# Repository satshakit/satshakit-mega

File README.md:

<div align="center"><h1 style="font-family: courier;" align="center">satshakit-mega</h1></div>
<div align="center"></div>
<div align="center"><i>An open source & fabbable ATMega2560 based microcontroller board.</i></div>

License
--
This work is licensed under the terms of the open source license: Creative Commons Attribution-ShareAlike 4.0 International ([CC BY-SA 4.0](https://creativecommons.org/licenses/by-sa/4.0/)).

Disclaimer  
--

<div class="align-justify">
This hardware/software is provided "as is", and you use the hardware/software at your own risk. Under no circumstances shall any author be liable for direct, indirect, special, incidental, or consequential damages resulting from the use, misuse, or inability to use this hardware/software, even if the authors have been advised of the possibility of such damages.</div>

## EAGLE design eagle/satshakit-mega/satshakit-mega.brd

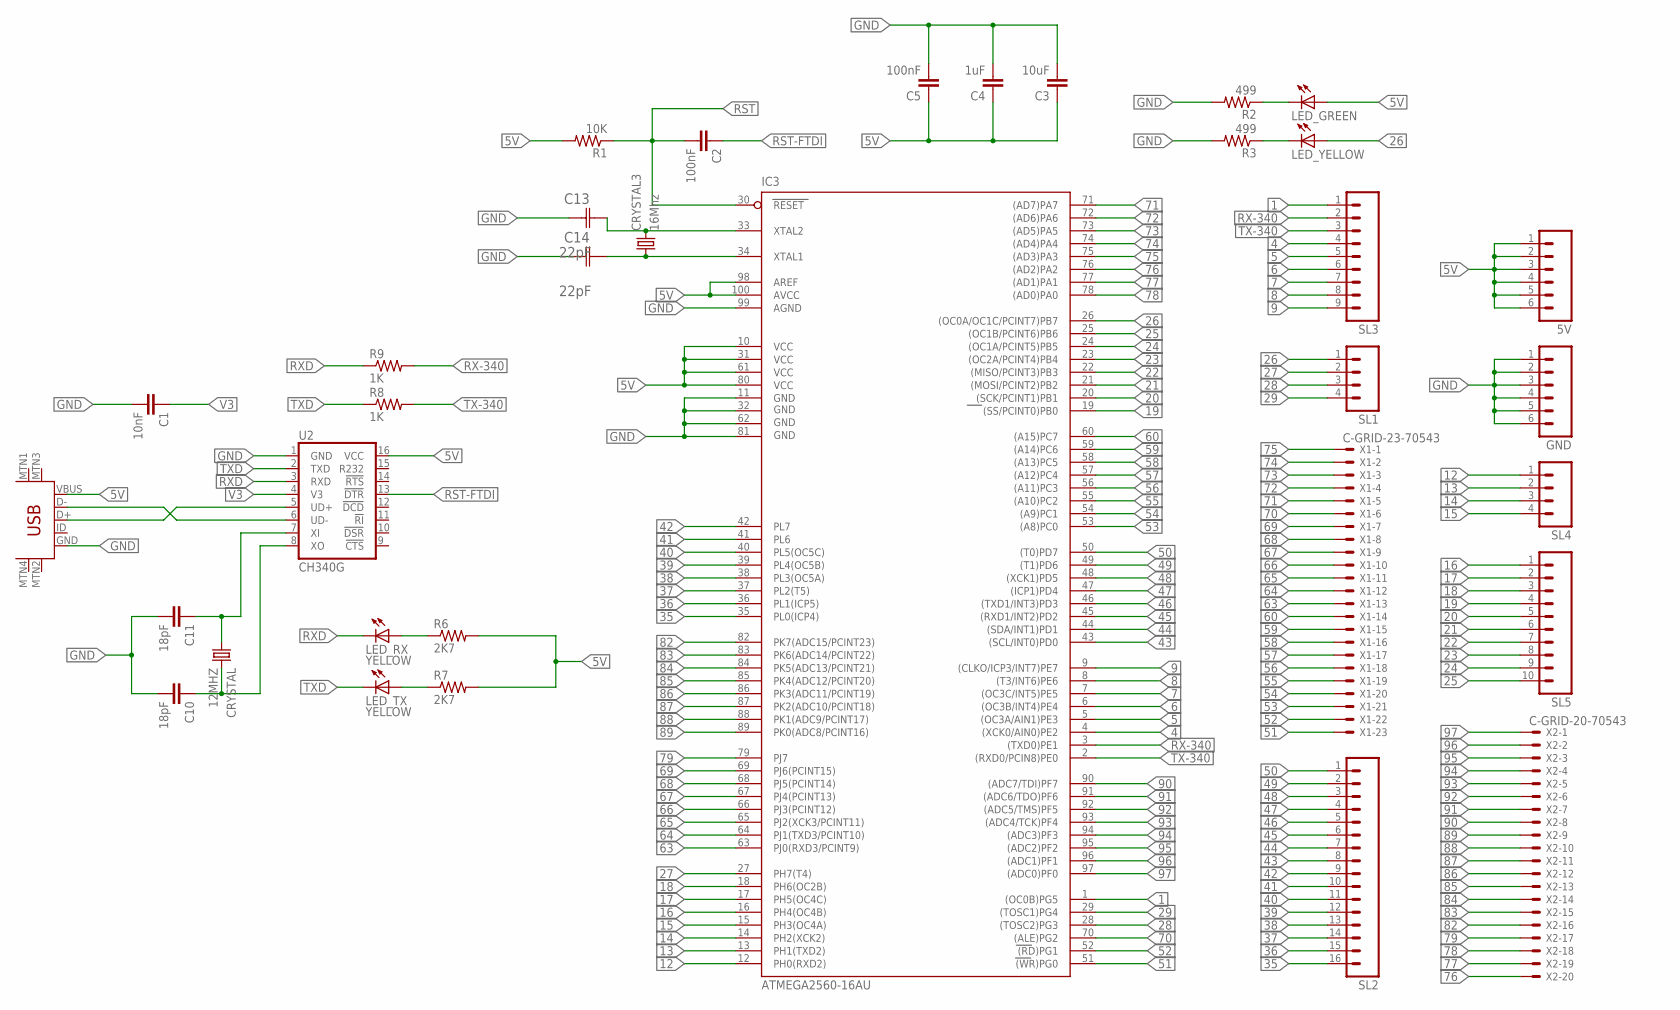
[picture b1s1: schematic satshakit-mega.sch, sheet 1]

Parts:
5V: M06; 06P
C1: 10nF; 1206
C2, C5: 100nF; 1206
C3: 10uF; 1206
C4: 1uF; 1206
C10, C11: 18pF; 1206
C13, C14: 22pF; CAPC3216X178N
CRYSTAL: 12MHZ; CSM-7X-DU
CRYSTAL3: 16Mhz; CSM-7X-DU
GND: M06; 06P
IC3: ATMEGA2560-16AU; TQFP100
LED_GREEN: LED1206; 1206
LED_RX: YELLOW; LED1206
LED_TX: YELLOW; LED1206
LED_YELLOW: LED1206; 1206
R1: 10K; R1206
R2, R3: 499; 1206
R6, R7: 2K7; R1206
R8, R9: 1K; R1206
SL1, SL4: M04; 04P
SL2: M16; 16P
SL3: M09; 09P
SL5: M10; 10P
U2: CH340G; SO016
U$7: USB-MINIB-5PIN; USB-MINIB
X1: C-GRID-23-70543; 70543-23
X2: C-GRID-20-70543; 70543-20

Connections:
1: IC3.1 ((OC0B)PG5), SL3.1
4: IC3.4 ((XCK0/AIN0)PE2), SL3.4
5: IC3.5 ((OC3A/AIN1)PE3), SL3.5
5V: 5V.1, 5V.2, 5V.3, 5V.4, 5V.5, 5V.6, C3.1, C4.1, C5.1, IC3.10 (VCC), IC3.31 (VCC1), IC3.61 (VCC2), IC3.80 (VCC3), IC3.98 (AREF), IC3.100 (AVCC), LED_GREEN.1 (A), R1.2, R6.2, R7.2, U2.16 (VCC), U$7.VBUS
6: IC3.6 ((OC3B/INT4)PE4), SL3.6
7: IC3.7 ((OC3C/INT5)PE5), SL3.7
8: IC3.8 ((T3/INT6)PE6), SL3.8
9: IC3.9 ((CLKO/ICP3/INT7)PE7), SL3.9
12: IC3.12 (PH0(RXD2)), SL4.1
13: IC3.13 (PH1(TXD2)), SL4.2
14: IC3.14 (PH2(XCK2)), SL4.3
15: IC3.15 (PH3(OC4A)), SL4.4
16: IC3.16 (PH4(OC4B)), SL5.1
17: IC3.17 (PH5(OC4C)), SL5.2
18: IC3.18 (PH6(OC2B)), SL5.3
19: IC3.19 ((SS/PCINT0)PB0), SL5.4
20: IC3.20 ((SCK/PCINT1)PB1), SL5.5
21: IC3.21 ((MOSI/PCINT2)PB2), SL5.6
22: IC3.22 ((MISO/PCINT3)PB3), SL5.7
23: IC3.23 ((OC2A/PCINT4)PB4), SL5.8
24: IC3.24 ((OC1A/PCINT5)PB5), SL5.9
25: IC3.25 ((OC1B/PCINT6)PB6), SL5.10
26: IC3.26 ((OC0A/OC1C/PCINT7)PB7), LED_YELLOW.1 (A), SL1.1
27: IC3.27 (PH7(T4)), SL1.2
28: IC3.28 ((TOSC2)PG3), SL1.3
29: IC3.29 ((TOSC1)PG4), SL1.4
35: IC3.35 (PL0(ICP4)), SL2.16
36: IC3.36 (PL1(ICP5)), SL2.15
37: IC3.37 (PL2(T5)), SL2.14
38: IC3.38 (PL3(OC5A)), SL2.13
39: IC3.39 (PL4(OC5B)), SL2.12
40: IC3.40 (PL5(OC5C)), SL2.11
41: IC3.41 (PL6), SL2.10
42: IC3.42 (PL7), SL2.9
43: IC3.43 ((SCL/INT0)PD0), SL2.8
44: IC3.44 ((SDA/INT1)PD1), SL2.7
45: IC3.45 ((RXD1/INT2)PD2), SL2.6
46: IC3.46 ((TXD1/INT3)PD3), SL2.5
47: IC3.47 ((ICP1)PD4), SL2.4
48: IC3.48 ((XCK1)PD5), SL2.3
49: IC3.49 ((T1)PD6), SL2.2
50: IC3.50 ((T0)PD7), SL2.1
51: IC3.51 ((WR)PG0), X1.23
52: IC3.52 ((RD)PG1), X1.22
53: IC3.53 ((A8)PC0), X1.21
54: IC3.54 ((A9)PC1), X1.20
55: IC3.55 ((A10)PC2), X1.19
56: IC3.56 ((A11)PC3), X1.18
57: IC3.57 ((A12)PC4), X1.17
58: IC3.58 ((A13)PC5), X1.16
59: IC3.59 ((A14)PC6), X1.15
60: IC3.60 ((A15)PC7), X1.14
63: IC3.63 (PJ0(RXD3/PCINT9)), X1.13
64: IC3.64 (PJ1(TXD3/PCINT10)), X1.12
65: IC3.65 (PJ2(XCK3/PCINT11)), X1.11
66: IC3.66 (PJ3(PCINT12)), X1.10
67: IC3.67 (PJ4(PCINT13)), X1.9
68: IC3.68 (PJ5(PCINT14)), X1.8
69: IC3.69 (PJ6(PCINT15)), X1.7
70: IC3.70 ((ALE)PG2), X1.6
71: IC3.71 ((AD7)PA7), X1.5
72: IC3.72 ((AD6)PA6), X1.4
73: IC3.73 ((AD5)PA5), X1.3
74: IC3.74 ((AD4)PA4), X1.2
75: IC3.75 ((AD3)PA3), X1.1
76: IC3.76 ((AD2)PA2), X2.20
77: IC3.77 ((AD1)PA1), X2.19
78: IC3.78 ((AD0)PA0), X2.18
79: IC3.79 (PJ7), X2.17
82: IC3.82 (PK7(ADC15/PCINT23)), X2.16
83: IC3.83 (PK6(ADC14/PCINT22)), X2.15
84: IC3.84 (PK5(ADC13/PCINT21)), X2.14
85: IC3.85 (PK4(ADC12/PCINT20)), X2.13
86: IC3.86 (PK3(ADC11/PCINT19)), X2.12
87: IC3.87 (PK2(ADC10/PCINT18)), X2.11
88: IC3.88 (PK1(ADC9/PCINT17)), X2.10
89: IC3.89 (PK0(ADC8/PCINT16)), X2.9
90: IC3.90 ((ADC7/TDI)PF7), X2.8
91: IC3.91 ((ADC6/TDO)PF6), X2.7
92: IC3.92 ((ADC5/TMS)PF5), X2.6
93: IC3.93 ((ADC4/TCK)PF4), X2.5
94: IC3.94 ((ADC3)PF3), X2.4
95: IC3.95 ((ADC2)PF2), X2.3
96: IC3.96 ((ADC1)PF1), X2.2
97: IC3.97 ((ADC0)PF0), X2.1
GND: C1.2, C3.2, C4.2, C5.2, C10.2, C11.2, C13.1 (C1), C14.1 (C1), GND.1, GND.2, GND.3, GND.4, GND.5, GND.6, IC3.11 (GND), IC3.32 (GND1), IC3.62 (GND2), IC3.81 (GND3), IC3.99 (AGND), R2.2, R3.2, U2.1 (GND), U$7.GND
unnamed: U2.5 (UD+), U$7.D+
unnamed: LED_RX.1 (A), R6.1
unnamed: U2.6 (UD-), U$7.D-
unnamed: C14.2 (C2), CRYSTAL3.1, IC3.34 (XTAL1)
unnamed: C13.2 (C2), CRYSTAL3.2, IC3.33 (XTAL2)
unnamed: LED_YELLOW.2 (C), R3.1
unnamed: LED_TX.1 (A), R7.1
unnamed: LED_GREEN.2 (C), R2.1
OSC_IN: C10.1, CRYSTAL.2, U2.8 (XO)
OSC_OUT: C11.1, CRYSTAL.1, U2.7 (XI)
RST: C2.2, IC3.30 (RESET), R1.1
RST-FTDI: C2.1, U2.13 (!DTR)
RX-340: IC3.3 ((TXD0)PE1), R9.2, SL3.2
RXD: LED_RX.2 (C), R9.1, U2.3 (RXD)
TX-340: IC3.2 ((RXD0/PCIN8)PE0), R8.2, SL3.3
TXD: LED_TX.2 (C), R8.1, U2.2 (TXD)
V3: C1.1, U2.4 (V3)

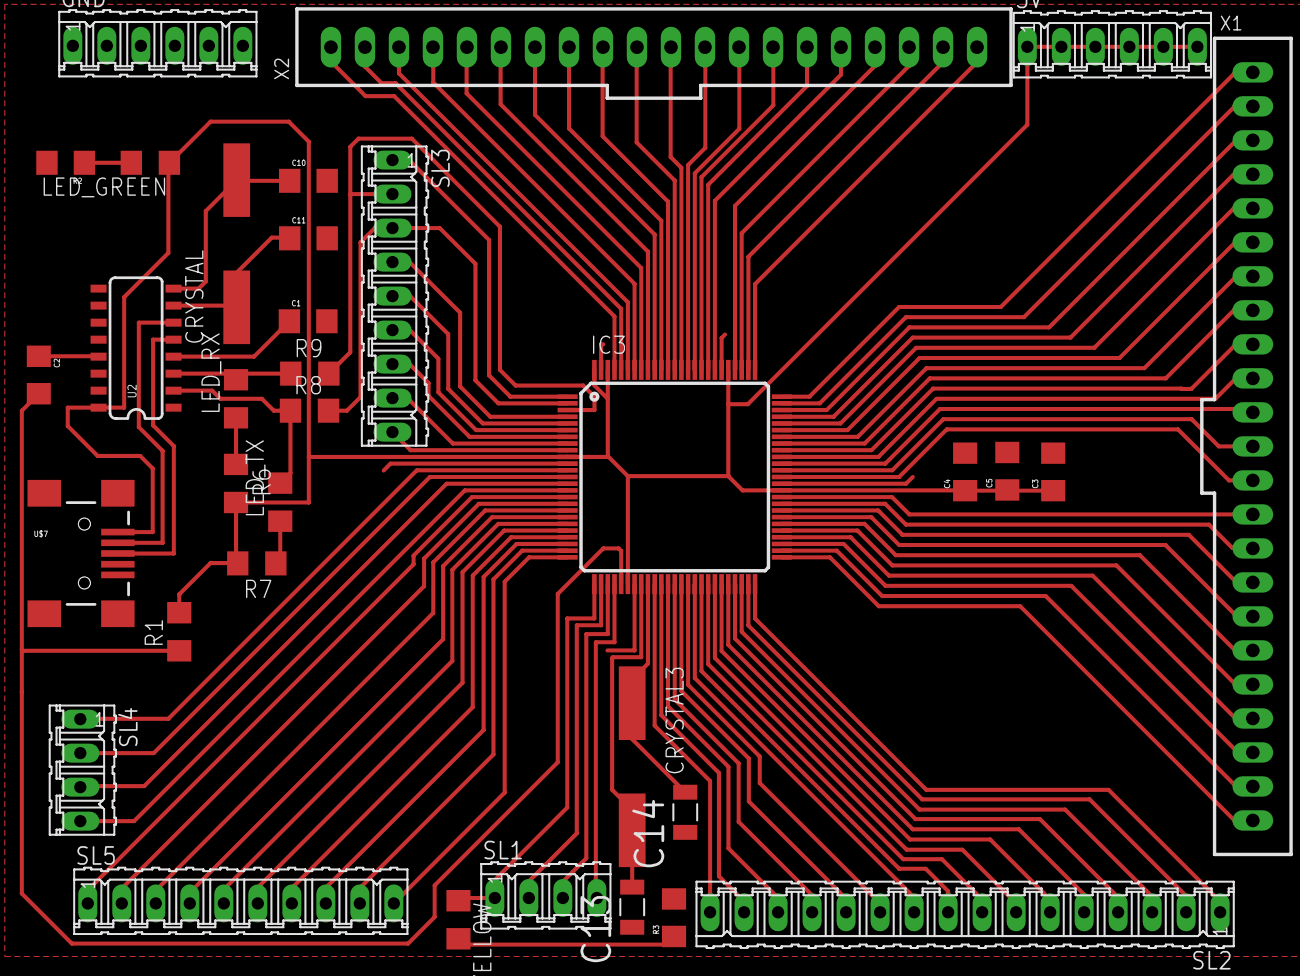
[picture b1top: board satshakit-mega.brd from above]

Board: 2 copper layers, 34 parts (0 on the bottom side), 103 nets.

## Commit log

2018-04-21 readme fixes
2018-04-21 added default led
2018-04-28 slighty change one trace
2018-04-28 added milling images
2018-05-02 updated eagle files
2018-05-02 added first picture
2020-05-31 license change

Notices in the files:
parts and their libraries:
01_SparkFun: Licensing: CC v3.0 Share-Alike You are welcome to use this library for commercial purposes.
SparkFun-DigitalIC: Licensing: Creative Commons ShareAlike 4.0 International - https://creativecommons.org/licenses/by-sa/4.0
